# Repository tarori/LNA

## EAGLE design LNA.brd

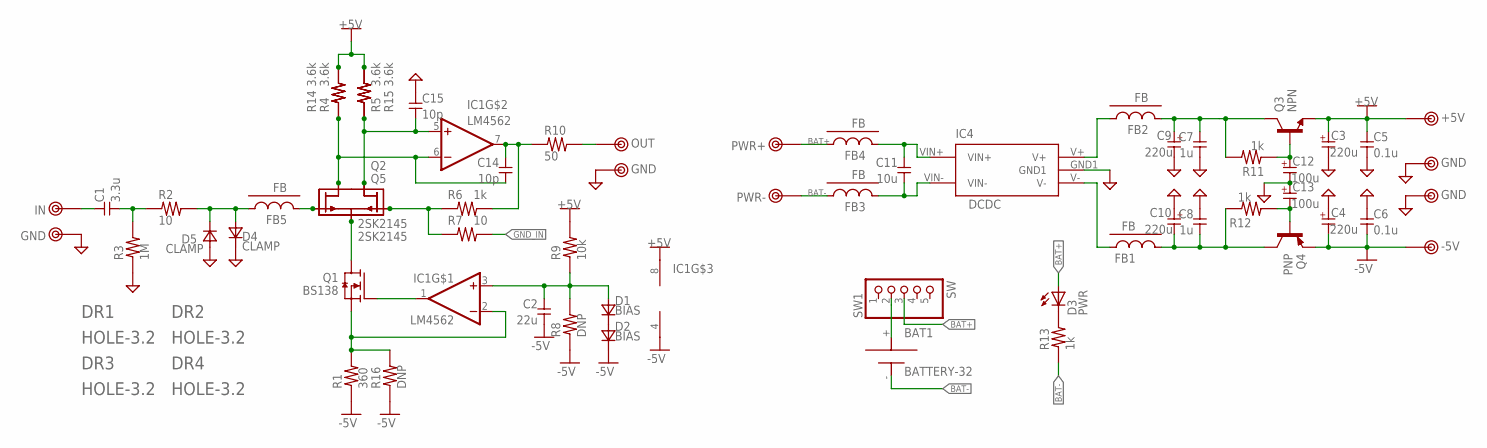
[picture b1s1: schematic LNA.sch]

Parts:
BAT1: BATTERY-32; BH-321
C1: 3.3u; 3225
C2: 22u; 3225
C3, C4, C9, C10: 220u; E2,5-8
C5, C6: 0.1u; 1608C
C7, C8: 1u; 1608C
C11: 10u; 2012
C12, C13: 100u; E2.5-6.5
C14, C15: 10p; 1608C
D1, D2: BIAS; SOD123
D3: PWR; D1608
D4, D5: CLAMP; SOD323
DR1, DR2, DR3, DR4: HOLE-3.2; HOLE_3.2
FB1, FB2, FB3, FB4, FB5: FB; 1608-FB
IC1: LM4562; SOP8
IC4: DCDC; DCDC2
Q1: BS138; SC59
Q2, Q5: 2SK2145; SOT23-5
Q3: NPN; SOT223
Q4: PNP; SOT223
R1: 360; 1608
R2, R7: 10; 1608
R3: 1M; 1608
R4, R5, R14, R15: 3.6k; 1608
R6, R11, R12, R13: 1k; 1608
R8, R16: DNP; 1608
R9: 10k; 1608
R10: 50; 1608
SW1: SW; 1X05-BIG
TP1: IN; TESTPIN
TP2, TP4: GND; TESTPIN
TP3: OUT; TESTPIN
TP5: PWR+; TESTPIN
TP6: PWR-; TESTPIN
TP7: +5V; TESTPIN-MID
TP8, TP9: GND; TESTPIN-MID
TP10: -5V; TESTPIN-MID

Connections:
+5V: C3.+ (1), C5.1, IC1.8 (V+), Q3.3 (E), R4.2, R5.2, R9.2, R14.2, R15.2, TP7.1
-5V: C2.2, C4.- (2), C6.2, D2.2 (K), IC1.4 (V-), Q4.3 (E), R1.1, R8.1, R16.1, TP10.1
BAT+: D3.A, FB4.1, SW1.3, TP5.1
BAT-: BAT1.-, FB3.1, R13.1, TP6.1
GND: C3.- (2), C4.+ (1), C5.2, C6.1, C7.2, C8.1, C9.- (2), C10.+ (1), C12.- (2), C13.+ (1), C15.1, D4.2 (K), D5.1 (A), IC4.GND1, R3.1, TP2.1, TP4.1, TP8.1, TP9.1
GND_IN: R7.2
unnamed: IC1.1 (OUT), Q1.1 (G)
unnamed: IC1.2 (-IN), Q1.2 (S), R1.2, R16.2
unnamed: BAT1.+, SW1.2
unnamed: D4.1 (A), D5.2 (K), FB5.1, R2.2
unnamed: C1.2, R2.1, R3.2
unnamed: C1.1, TP1.1
unnamed: C15.2, IC1.5 (+IN), Q2.1 (D1), Q5.3 (D2), R5.1, R15.1
unnamed: FB5.2, Q2.4 (G2), Q5.5 (G1)
unnamed: Q2.5 (G1), Q5.4 (G2), R6.1, R7.1
unnamed: C2.1, D1.1 (A), IC1.3 (+IN), R8.2, R9.1
unnamed: C14.1, IC1.7 (OUT), R6.2, R10.1
unnamed: C8.2, C10.- (2), FB1.2, Q4.2 (C), Q4.4 (C), R12.2
unnamed: C7.1, C9.+ (1), FB2.2, Q3.2 (C), Q3.4 (C), R11.2
unnamed: FB1.1, IC4.V-
unnamed: FB2.1, IC4.V+
unnamed: R10.2, TP3.1
unnamed: D1.2 (K), D2.1 (A)
unnamed: D3.K, R13.2
unnamed: C11.1, FB4.2, IC4.VIN+
unnamed: C11.2, FB3.2, IC4.VIN-
unnamed: Q1.3 (D), Q2.2 (S), Q5.2 (S)
unnamed: C12.+ (1), Q3.1 (B), R11.1
unnamed: C13.- (2), Q4.1 (B), R12.1
unnamed: C14.2, IC1.6 (-IN), Q2.3 (D2), Q5.1 (D1), R4.1, R14.1

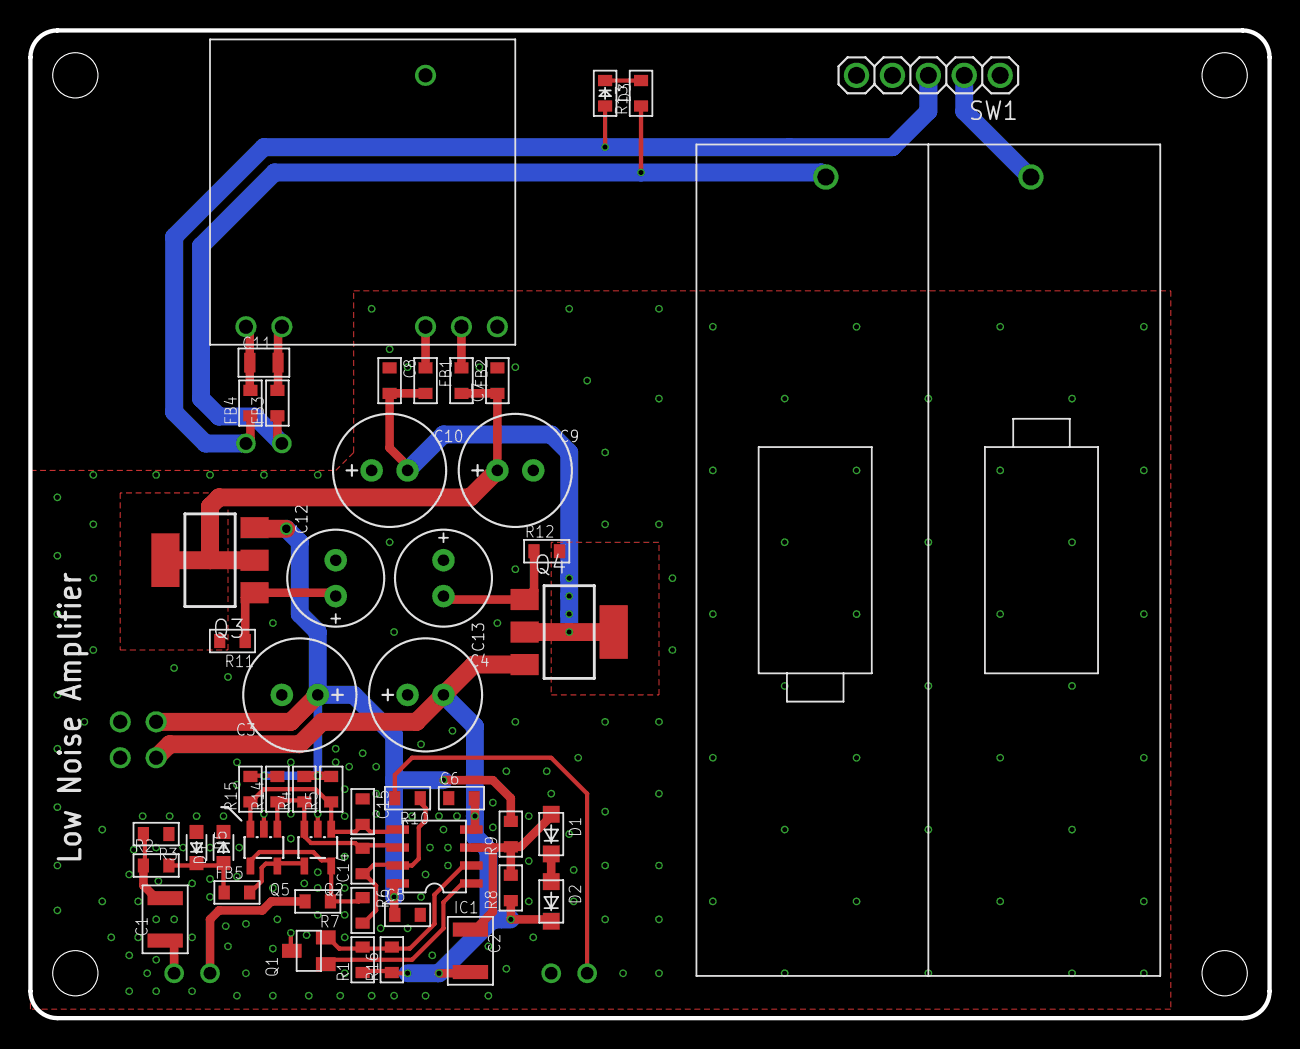
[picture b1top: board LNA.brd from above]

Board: 4 copper layers, 87.6 x 69.9 mm, 64 parts (0 on the bottom side), 29 nets.

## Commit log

2024-09-08 init
